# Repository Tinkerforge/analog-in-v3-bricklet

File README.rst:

Analog In Bricklet 3.0
======================

This repository contains the firmware source code and the hardware design
files. The documentation generator configs can be found at
https://github.com/Tinkerforge/generators

Repository Content
------------------

software/:
 * examples/: Examples for all supported languages
 * build/: Compiled files
 * src/: Source code of firmware
 * Makefile: Makefile to build project

hardware/:
 * Contains KiCad project files and additionally schematics as PDF

datasheets/:
 * Contains datasheets for sensors and complex ICs that are used

Hardware
--------

The hardware is designed with the open source EDA Suite KiCad
(http://www.kicad.org). Before you are able to open the files,
you have to install the Tinkerforge kicad-libraries
(https://github.com/Tinkerforge/kicad-libraries). You can either clone
them directly in hardware/ or clone them in a separate folder and
symlink them into hardware/
(ln -s kicad_path/kicad-libraries project_path/hardware). After that you
can open the .pro file in hardware/ with KiCad and from there view and
modify the schematics and the PCB layout.

Software
--------

If you want to do your own Brick/Bricklet firmware development we highly
recommend that you use our build environment setup script and read the
tutorial (https://www.tinkerforge.com/en/doc/Tutorials/Tutorial_Build_Environment/Tutorial.html).

To compile the C code we recommend you to install the newest GNU Arm Embedded
Toolchain (https://launchpad.net/gcc-arm-embedded/+download).
You also need to install bricklib2 (https://github.com/Tinkerforge/bricklib2).

You can either clone it directly in software/src/ or clone it in a
separate folder and symlink it into software/src/
(ln -s bricklib_path/bricklib2 project_path/software/src/). Finally make sure to
have CMake installed (http://www.cmake.org/cmake/resources/software.html).

After that you can build the firmware by invoking make in software/.
The firmware (.zbin) can then be found in software/build/ and uploaded
with brickv (click button "Flashing" on start screen).

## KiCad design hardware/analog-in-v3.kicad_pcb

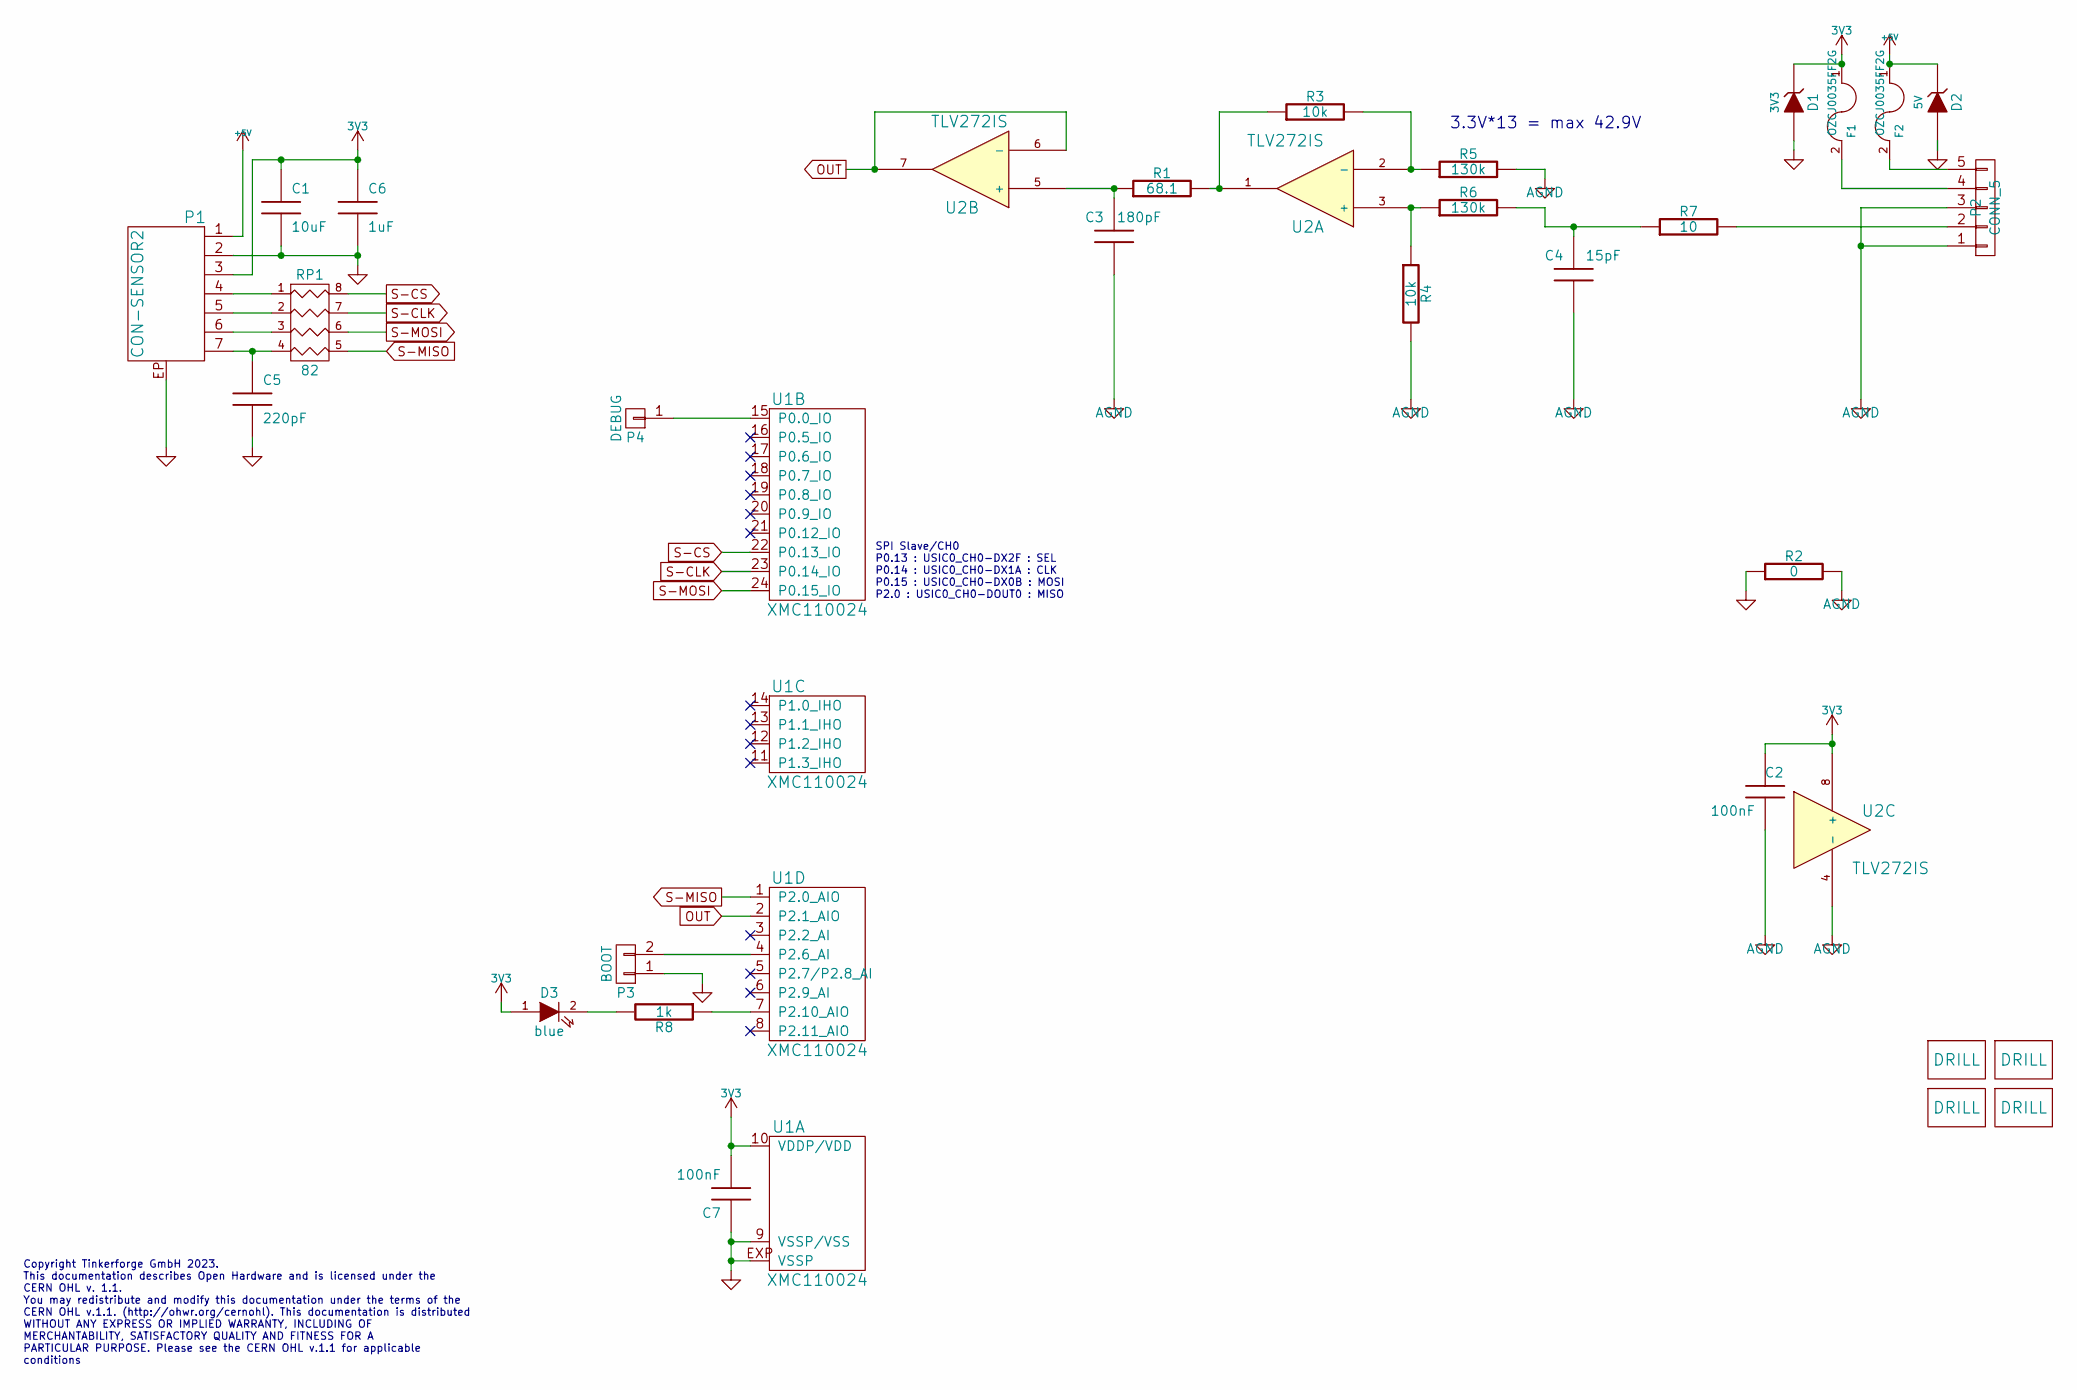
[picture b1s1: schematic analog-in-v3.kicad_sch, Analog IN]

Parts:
C1: 10uF; C0805
C2, C7: 100nF; C0603F
C3: 180pF; C0603F
C4: 15pF; C0603F
C5: 220pF; C0402F
C6: 1uF; C0603F
D1: 3V3; MiniMelf
D2: 5V; MiniMelf
D3: blue; D0603F
F1, F2: OZCJ0035FF2G; F1206
P1: CON-SENSOR2
P2: CONN_5; AKL_5_5
P3: BOOT; SolderJumper
P4: DEBUG; DEBUG_PAD
R1: 68.1; R0603F
R2: 0; R0603F
R3, R4: 10k; R0603F
R5, R6: 130k; R0603F
R7: 10; R0603F
R8: 1k; R0603F
RP1: 82; 4X0402
U1: XMC110024; QFN24-4x4mm-0.5mm
U2: TLV272IS; SOIC8
U3, U4, U5, U6: DRILL; DRILL_NP

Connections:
3V3: C1.1, C2.2, C6.1, C7.2, D1.2 (K), D3.1 (A), F1.1, P1.3, U1.10 (VDDP/VDD), U2.8 (+)
+5V: D2.2 (K), F2.1, P1.1
AGND: C2.1, C3.1, C4.1, P2.1, P2.3, R2.2, R4.2, R5.2, U2.4 (-)
GND: C1.2, C5.2, C6.2, C7.1, D1.1 (A), D2.1 (A), P1.2, P1.EP, P3.1, R2.1, U1.9 (VSSP/VSS), U1.EXP (VSSP)
unnamed: C3.2, R1.1, U2.5 (+)
unnamed: C4.2, R6.2, R7.1
unnamed: C5.1, P1.7, RP1.4
unnamed: D3.2 (K), R8.2
unnamed: F1.2, P2.4
unnamed: F2.2, P2.5
unnamed: P1.4, RP1.1
unnamed: P1.5, RP1.2
unnamed: P1.6, RP1.3
unnamed: P2.2, R7.2
unnamed: P3.2, U1.4 (P2.6_AI)
unnamed: P4.1, U1.15 (P0.0_IO)
unnamed: R1.2, R3.1, U2.1
unnamed: R3.2, R5.1, U2.2 (-)
unnamed: R4.1, R6.1, U2.3 (+)
unnamed: R8.1, U1.7 (P2.10_AIO)
OUT: U1.2 (P2.1_AIO), U2.6 (-), U2.7
S-CLK: RP1.7 (R2), U1.23 (P0.14_IO)
S-CS: RP1.8 (R1), U1.22 (P0.13_IO)
S-MISO: RP1.5 (R4), U1.1 (P2.0_AIO)
S-MOSI: RP1.6 (R3), U1.24 (P0.15_IO)

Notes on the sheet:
3.3V*13 = max 42.9V
Copyright Tinkerforge GmbH 2023. This documentation describes Open Hardware and is licensed under the CERN OHL v. 1.1. You may redistribute and modify this documentation under the terms of the CERN OHL v.1.1. (http://ohwr.org/cernohl). This documentation is distributed WITHOUT ANY EXPRESS OR IMPLIE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
SPI Slave/CH0 P0.13 : USIC0_CH0-DX2F : SEL P0.14 : USIC0_CH0-DX1A : CLK P0.15 : USIC0_CH0-DX0B : MOSI P2.0 : USIC0_CH0-DOUT0 : MISO

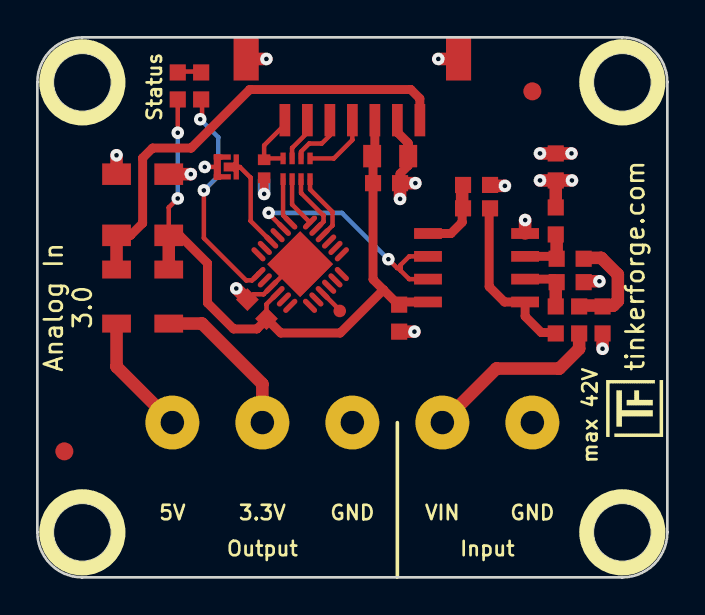
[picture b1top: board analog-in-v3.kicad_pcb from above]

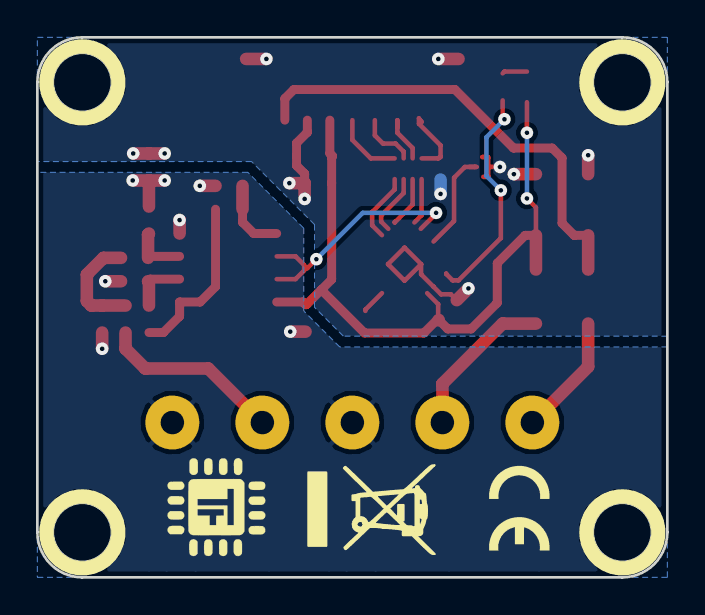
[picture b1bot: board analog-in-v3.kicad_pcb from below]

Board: 2 copper layers, 35.0 x 30.0 mm, 35 parts (2 on the bottom side), 25 nets.

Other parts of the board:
Fiducial_Mark: VAL**; Fiducial_Mark
Fiducial_Mark#2: VAL**; Fiducial_Mark
VAL: CE_5mm
VAL#2: WEEE_7mm

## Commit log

2017-09-14 Add schematic
2017-09-14 Add missing footprint
2017-09-15 Change LED pin, optical adjustments
2017-09-15 Add PCB
2017-09-15 Fix ground planes
2017-09-15 update license date
2017-09-15 small routing changes
2017-09-15 Fix paths
2017-10-13 Add initial stub implementation
2017-10-18 change led position
2017-10-23 Fix 3d model (R0603F instead of C0603F)
2017-10-23 Add 3d model (*.step *.FCStd)
2017-10-26 specify processor type
2017-10-27 Add Analog In API and implementation
2018-01-11 Add examples
2018-01-30 Update examples
2018-02-16 Minor optical adjustments
2018-02-16 Add schematic (PDF)
2018-02-19 javascript: Close div tag correctly
2018-02-20 Cleanup KiCad libraries config
    Ensure LibDir=kicad-libraries and LibName1=tinkerforge.
    Remove special library.
2018-03-05 Remove unused flash-size define
2018-05-11 Rename files
2018-05-24 perl: Use strict in examples
2018-05-25 Add LabVIEW examples
2018-05-25 labview: Remove bogus SetDebouncePeriod call
2018-06-06 Adapt to bricklet2 callback-value changes to fix wrong length of get-voltage packet
2018-06-06 Update changelog and version
2018-06-07 Add date ref for version 2.0.1 to changelog
2018-06-18 Change capacitor footprint(s) to C0402F
2018-06-28 Fix readme
2018-07-11 Add Makefile with docker support
2018-07-11 Update directory structure and build instructions
2018-07-11 Remove obsolete generate_makefile scripts
2018-10-04 Increase version for new release (changes in bricklib2)
2018-10-04 Add rev to changelog
2018-11-06 Add rust examples
2018-11-07 rust: Accept host names for ip connection, fix naming inconsistencies
2018-11-07 rust: Rename callback receivers.
2018-12-14 Add go examples.
2018-12-14 go: Fix printf parameters.
2018-12-18 go: Change import path.
2018-12-18 go: Change import path again.
2018-12-20 rust: Reformat examples.
2019-01-18 fix status text
2019-01-24 mqtt: Add examples.
2019-01-24 mqtt: Fix example header.
2019-01-24 mqtt: Remove executable bit in example permissions.
2019-01-24 go: Minor example fixes.
2019-01-24 mqtt: Minor example fixes.
2019-02-07 fixed schematic, added symlib table
2019-03-28 mqtt: Fix whitespace.
2019-08-22 c: Adapt to bindings changes
2020-01-13 examples: Use python3 input instead of python2 raw_input.
2020-01-13 examples: mqtt: Remove trailing whitespace.
2020-08-19 Add uc examples.
2020-08-25 uc: Fix whitespace
2020-08-27 uc: Fix warnings.
2020-09-02 uc: Add example driver note.
2020-10-16 uc: Fix divisor type.
2021-10-25 Update KiCad link
    https://www.kicad.org/blog/2021/10/Avoid-links-to-former-kicad-domain/
2022-04-19 examples: uc: Rename TF_HalContext to TF_HAL.
2022-04-27 uc: Adapt to bindings changes
2022-07-06 Add license files.
2023-01-23 New standart layout. Switched to Kicad 6
2023-01-25 Data Cleanup

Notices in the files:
hardware/analog-in-v3.kicad_pcb:
Licensed under CERN OHL v.1.1
Copyright (©) 2023, T.Schneidermann
